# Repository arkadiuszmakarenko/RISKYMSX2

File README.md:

# RISKYMSX2

The RISKYMSX2 cartridge PROTOTYPE by Arek Makarenko is a compact MSX flash ROM cartridge based on the inexpensive CH32V467VCT6 RISC-V MCU which can be easily programmed from a MSX computer using a FAT formatted USB pen drive containing ROM files.
This chip is 200Mhz with 8MB PSRAM onboard, USB HS, and I will be figting to meet all needed MSX timings. Wish me luck!

DO NOT BUILD AT THIS STAGE unless you can create own firmware!

<<<<<<< HEAD
Piout ChatGPT
U1 CONNECTIONS
KiCad 10 schematic: RISKYMSX2.kicad_sch
Component: CH32V467VET6

Pin	MCU pin	Connection
----	-------	----------
1	PE2(FT)	WR
2	PE3(FT)	WAIT
3	PE4(FT)	~{RESET}
4	PE5(FT)	MREQ
5	PE6(FT)	M1
6	VBAT	unlabelled connection
7	PC13	NC
8	PC14	NC
9	PC15	NC
10	VSS	unlabelled connection
11	VDD	unlabelled connection
12	OSC_IN	X1 (crystal connection)
13	OSC_OUT	X1 (crystal connection)
14	~{NRST}	NRST
15	PC0	NC
16	PC1	NC
17	PC2	NC
18	PC3	NC
19	VSSA	unlabelled connection
20	VREF-	unlabelled connection
21	VREF+	unlabelled connection
22	VDDA	unlabelled connection
23	PA0	LEDFLASH
24	PA1	NC
25	PA2	NC
26	PA3	NC
27	VSS	unlabelled connection
28	VDD	unlabelled connection
29	PA4(HS)	SCC_OUT
30	PA5(HS)	NC
31	PA6(HS)	NC
32	PA7(HS)	NC
33	PC4	NC
34	PC5	NC
35	PB0	NC
36	PB1	NC
37	BOOT1(FT)	GND
38	PE8(FT)	IORQ
39	PE9(FT)	BDIR
40	VDDK	unlabelled connection
41	VSS	unlabelled connection
42	MDIRN	NC
43	MDIRP	NC
44	MDITN	NC
45	MDITP	NC
46	VDD	unlabelled connection
47	VSS	unlabelled connection
48	VDD18	unlabelled connection
49	PB10(FT)	D2
50	PB11(FT)	D3
51	PD8(FT)	A8
52	PB12(FT)	D4
53	PB13(FT)	D5
54	PB14(FT)	D6
55	PB15(FT)	D7
56	PD9(FT)	A9
57	PD10(FT)	A10
58	PD11(FT)	A11
59	PD12(FT)	A12
60	PD13(FT)	A13
61	PD14(FT)	A14
62	PD15(FT)	A15
63	PC6(FT)	CS2
64	PC7(FT)	RFSH
65	PC8(FT)	SLOTINT
66	PC9(FT)	SLOTCLK
67	PA8(FT)	NC
68	PA9(FT)	USART_TX
69	PA10(FT)	USART_RX
70	PA11	USB1_DM
71	PA12	USB1_DP
72	SWDIO(FT)	SWDIO
73	PE10(FT)	CS1
74	PE11(FT)	CS12
75	VDD	unlabelled connection
76	SWCLK(FT)	SWCLK
77	PA15(FT)	NC
78	PC10(FT)	NC
79	PC11(FT)	NC
80	PC12(FT)	NC
81	PD0(FT)	A0
82	PD1(FT)	A1
83	PD2(FT)	A2
84	PD3(FT)	A3
85	PD4(FT)	A4
86	PD5(FT)	A5
87	PD6(FT)	A6
88	PD7(FT)	A7
89	PB3(FT)	NC
90	PB4(FT)	NC
91	PB5(FT)	NC
92	PB6	NC
93	PB7	NC
94	BOOT0(FT)	BOOT0
95	PB8(FT)	D0
96	PB9(FT)	D1
97	PE0(FT)	~{EXSLTSL}
98	PE1(FT)	RD
99	VSS	unlabelled connection
100	VDD	unlabelled connection

Notes:
- NC = explicit KiCad no-connect marker.
- 'unlabelled connection' = the pin is wired, but no named net label was found on that net.
- X1 = the crystal connected to U1 pins 12 and 13.

Important: In this schematic U1 pin 34 (PC5) is NC; A0 is U1 pin 81 (PD0).
=======

>>>>>>> 920e6b2be6f260394af7e6f48916e51129308a6d

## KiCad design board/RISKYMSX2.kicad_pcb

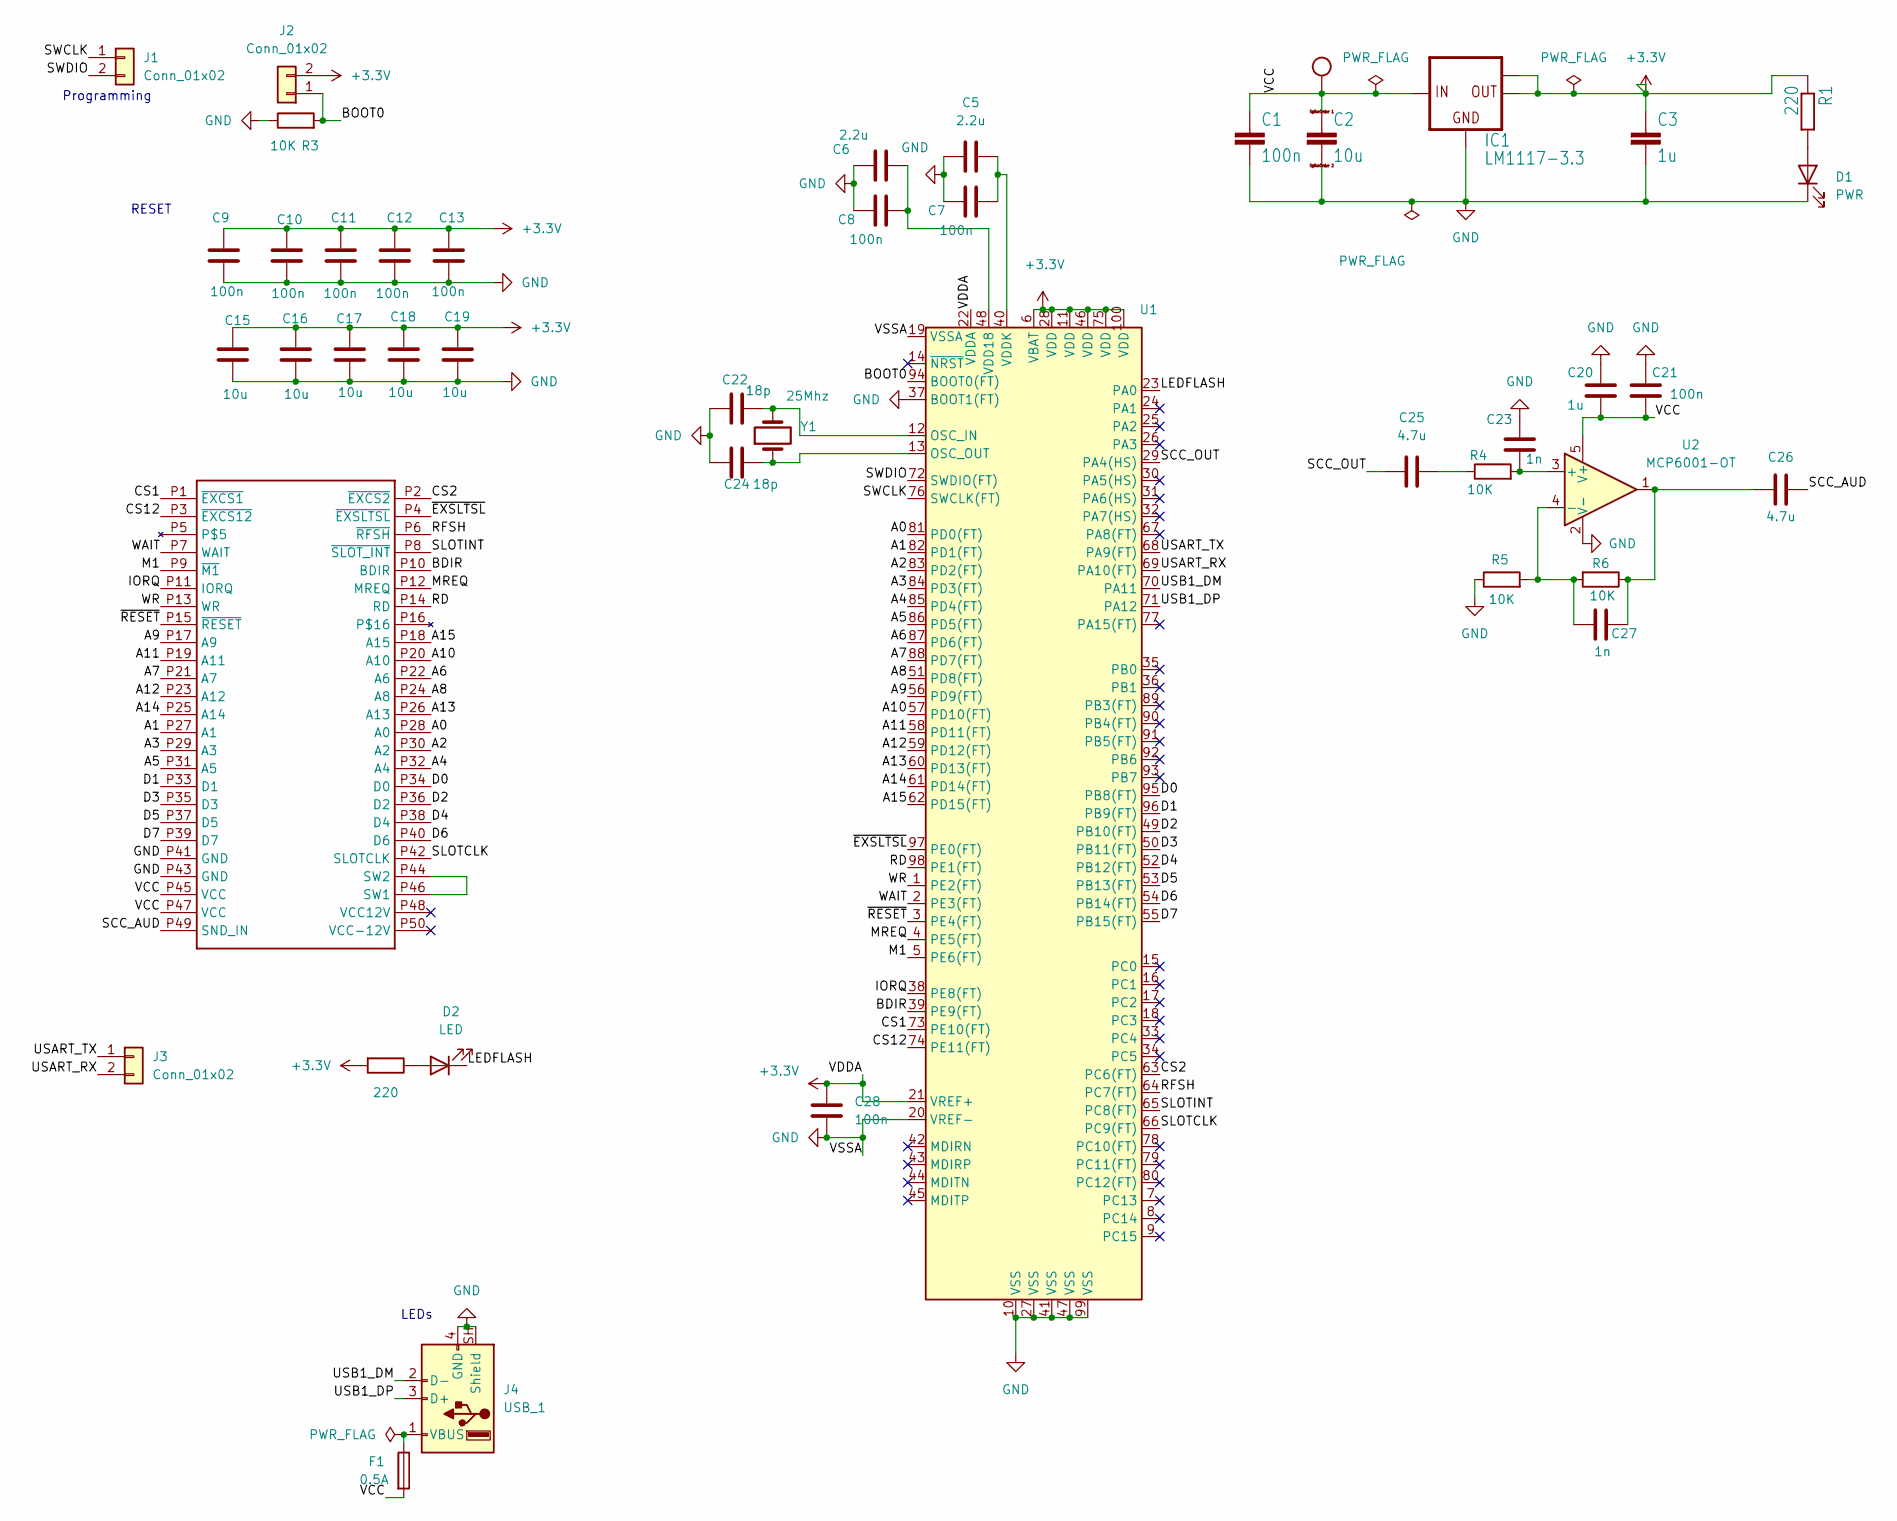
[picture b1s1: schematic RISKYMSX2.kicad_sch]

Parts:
C1: 100n; C_1206_3216Metric
C2, C15, C16, C17, C18, C19: 10u; C_0603_1608Metric_Pad1.08x0.95mm_HandSolder
C3: 1u; C_1206_3216Metric
C5, C6: 2.2u; C_0603_1608Metric_Pad1.08x0.95mm_HandSolder
C7, C8, C9, C10, C11, C12, C13, C21, C28: 100n; C_0603_1608Metric_Pad1.08x0.95mm_HandSolder
C20: 1u; C_0603_1608Metric_Pad1.08x0.95mm_HandSolder
C22, C24: 18p; C_0603_1608Metric_Pad1.08x0.95mm_HandSolder
C23, C27: 1n; C_0603_1608Metric_Pad1.08x0.95mm_HandSolder
C25, C26: 4.7u; C_0603_1608Metric_Pad1.08x0.95mm_HandSolder
CN1: MSX_CART
D1: PWR; LED_1206_3216Metric_Pad1.42x1.75mm_HandSolder
D2: LED; LED_1206_3216Metric_Pad1.42x1.75mm_HandSolder
F1: 0.5A; Fuse_1206_3216Metric_Pad1.42x1.75mm_HandSolder
IC1: LM1117-3.3; SOT223
J1, J2, J3: Conn_01x02; PinHeader_1x02_P2.54mm_Vertical
J4: USB_1; USB_A_Molex_67643_Horizontal
R1, R7: 220; R_0603_1608Metric_Pad0.98x0.95mm_HandSolder
R3, R4, R5, R6: 10K; R_0603_1608Metric_Pad0.98x0.95mm_HandSolder
U1: CH32V467VET6; LQFP-100_14x14mm_P0.5mm
U2: MCP6001-OT; SOT-23-5
Y1: 25Mhz; Crystal_HC49-4H_Vertical

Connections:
+3.3V: C3.1, C9.1, C10.1, C11.1, C12.1, C13.1, C15.1, C16.1, C17.1, C18.1, C19.1, C28.1, IC1.2 (OUT), IC1.TAB (OUT1), J2.2, R1.1, R7.2, U1.6 (VBAT), U1.11 (VDD), U1.21 (VREF+), U1.22 (VDDA), U1.28 (VDD), U1.46 (VDD), U1.75 (VDD), U1.100 (VDD)
/A0: CN1.P28 (A0), U1.81 (PD0(FT))
/A1: CN1.P27 (A1), U1.82 (PD1(FT))
/A2: CN1.P30 (A2), U1.83 (PD2(FT))
/A3: CN1.P29 (A3), U1.84 (PD3(FT))
/A4: CN1.P32 (A4), U1.85 (PD4(FT))
/A5: CN1.P31 (A5), U1.86 (PD5(FT))
/A6: CN1.P22 (A6), U1.87 (PD6(FT))
/A7: CN1.P21 (A7), U1.88 (PD7(FT))
/A8: CN1.P24 (A8), U1.51 (PD8(FT))
/A9: CN1.P17 (A9), U1.56 (PD9(FT))
/A10: CN1.P20 (A10), U1.57 (PD10(FT))
/A11: CN1.P19 (A11), U1.58 (PD11(FT))
/A12: CN1.P23 (A12), U1.59 (PD12(FT))
/A13: CN1.P26 (A13), U1.60 (PD13(FT))
/A14: CN1.P25 (A14), U1.61 (PD14(FT))
/A15: CN1.P18 (A15), U1.62 (PD15(FT))
/BDIR: CN1.P10 (BDIR), U1.39 (PE9(FT))
/BOOT0: J2.1, R3.2, U1.94 (BOOT0(FT))
/CS1: CN1.P1 (~EXCS1), U1.73 (PE10(FT))
/CS2: CN1.P2 (~EXCS2), U1.63 (PC6(FT))
/CS12: CN1.P3 (~EXCS12), U1.74 (PE11(FT))
/D0: CN1.P34 (D0), U1.95 (PB8(FT))
/D1: CN1.P33 (D1), U1.96 (PB9(FT))
/D2: CN1.P36 (D2), U1.49 (PB10(FT))
/D3: CN1.P35 (D3), U1.50 (PB11(FT))
/D4: CN1.P38 (D4), U1.52 (PB12(FT))
/D5: CN1.P37 (D5), U1.53 (PB13(FT))
/D6: CN1.P40 (D6), U1.54 (PB14(FT))
/D7: CN1.P39 (D7), U1.55 (PB15(FT))
/IORQ: CN1.P11 (IORQ), U1.38 (PE8(FT))
/LEDFLASH: D2.1 (K), U1.23 (PA0)
/M1: CN1.P9 (~M1), U1.5 (PE6(FT))
/MREQ: CN1.P12 (MREQ), U1.4 (PE5(FT))
/RD: CN1.P14 (RD), U1.98 (PE1(FT))
/RFSH: CN1.P6 (~RFSH), U1.64 (PC7(FT))
/SCC_AUD: C26.2, CN1.P49 (SND_IN)
/SCC_OUT: C25.1, U1.29 (PA4(HS))
/SLOTCLK: CN1.P42 (SLOTCLK), U1.66 (PC9(FT))
/SLOTINT: CN1.P8 (~SLOT_INT), U1.65 (PC8(FT))
/SWCLK: J1.1, U1.76 (SWCLK(FT))
/SWDIO: J1.2, U1.72 (SWDIO(FT))
/USART_RX: J3.2, U1.69 (PA10(FT))
/USART_TX: J3.1, U1.68 (PA9(FT))
/USB1_DM: J4.2 (D-), U1.70 (PA11)
/USB1_DP: J4.3 (D+), U1.71 (PA12)
/WAIT: CN1.P7 (WAIT), U1.2 (PE3(FT))
/WR: CN1.P13 (WR), U1.1 (PE2(FT))
/~EXSLTSL: CN1.P4 (~EXSLTSL), U1.97 (PE0(FT))
/~RESET: CN1.P15 (~RESET), U1.3 (PE4(FT))
GND: C1.2, C2.2, C3.2, C5.1, C6.1, C7.1, C8.1, C9.2, C10.2, C11.2, C12.2, C13.2, C15.2, C16.2, C17.2, C18.2, C19.2, C20.1, C21.1, C22.1, C23.2, C24.1, C28.2, CN1.P41 (GND), CN1.P43 (GND), D1.1 (K), IC1.1 (GND), J4.4 (GND), J4.SH (Shield), R3.1, R5.1, U1.10 (VSS), U1.19 (VSSA), U1.20 (VREF-), U1.27 (VSS), U1.37 (BOOT1(FT)), U1.41 (VSS), U1.47 (VSS), U1.99 (VSS), U2.2 (V-)
unnamed: C25.2, R4.1
unnamed: C26.1, C27.2, R6.1, U2.1
unnamed: CN1.P44 (SW2), CN1.P46 (SW1)
unnamed: D1.2 (A), R1.2
unnamed: D2.2 (A), R7.1
unnamed: F1.1, J4.1 (VBUS)
unnamed: C22.2, U1.12 (OSC_IN), Y1.2
unnamed: C24.2, U1.13 (OSC_OUT), Y1.1
unnamed: C6.2, C8.2, U1.48 (VDD18)
unnamed: C5.2, C7.2, U1.40 (VDDK)
unnamed: C23.1, R4.2, U2.3 (+)
unnamed: C27.1, R5.2, R6.2, U2.4 (-)
VCC: C1.1, C2.1, C20.2, C21.2, CN1.P45 (VCC), CN1.P47 (VCC), F1.2, IC1.3 (IN), U2.5 (V+)

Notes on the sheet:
RESET
Programming
LEDs

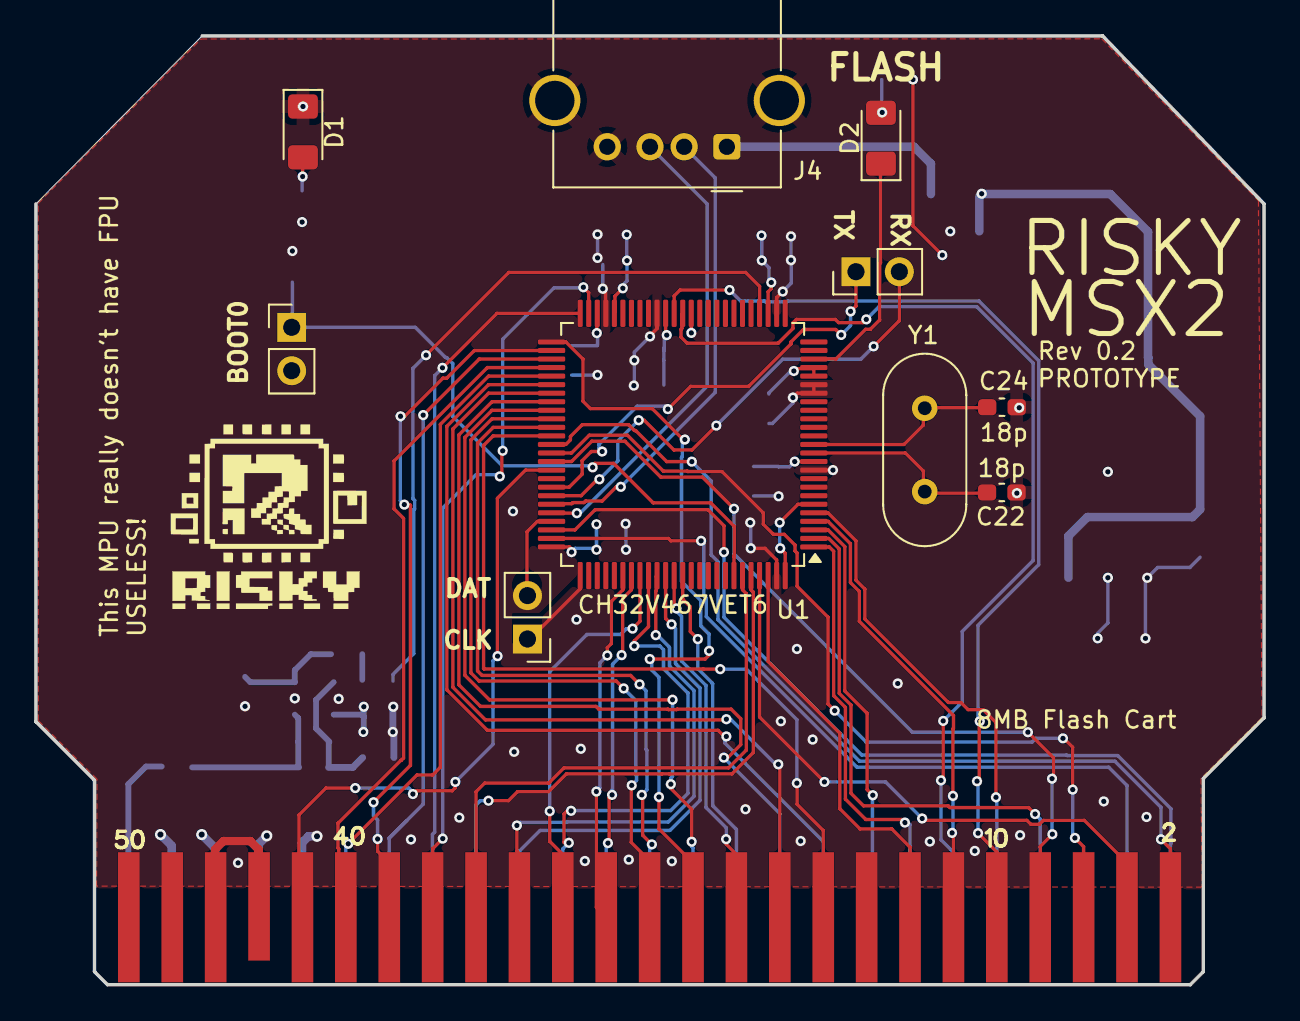
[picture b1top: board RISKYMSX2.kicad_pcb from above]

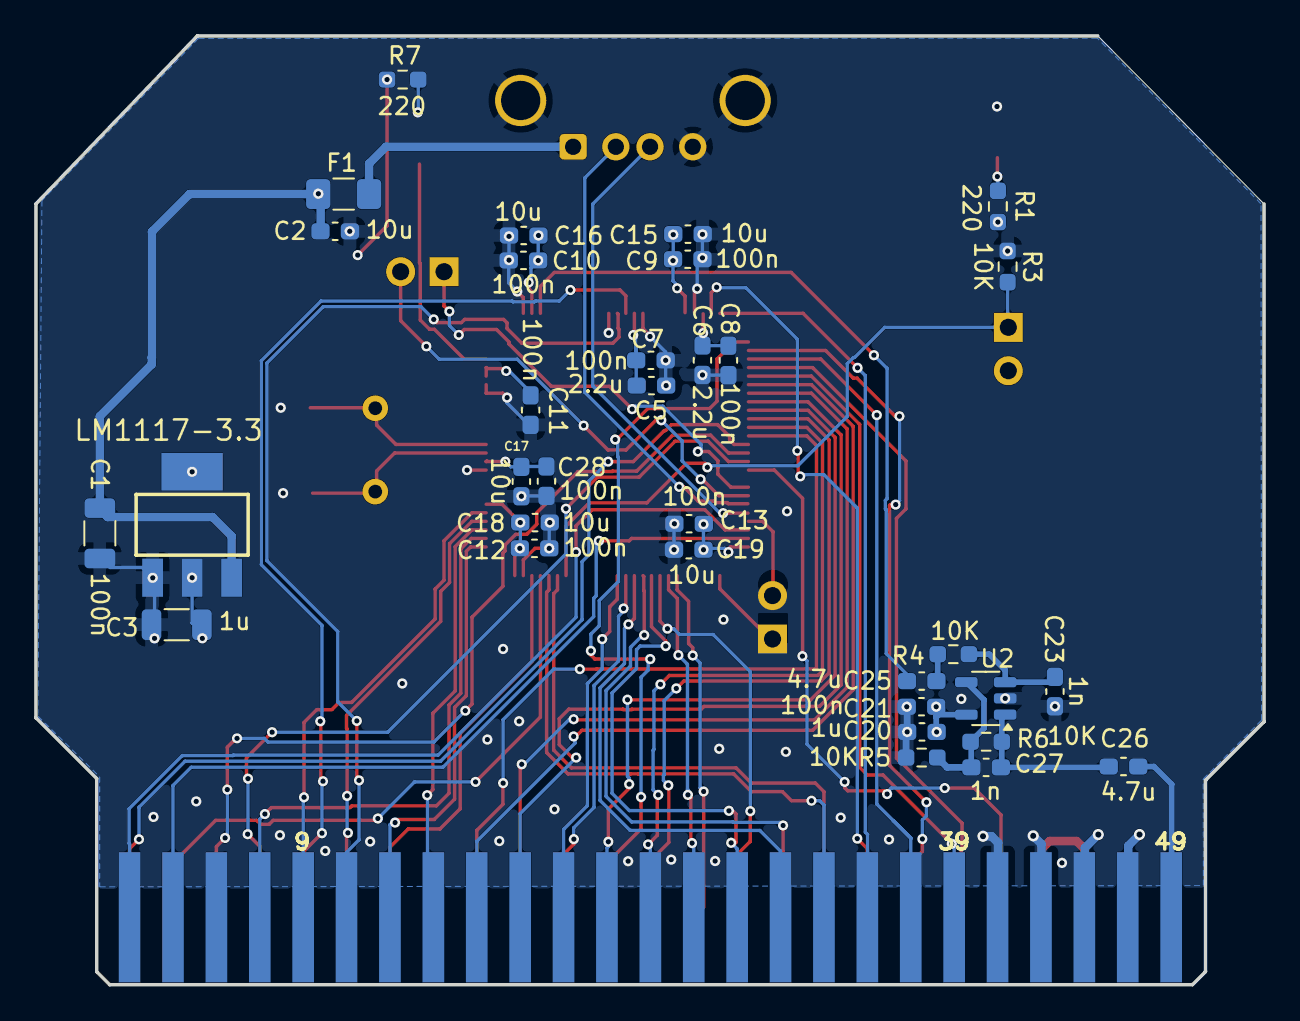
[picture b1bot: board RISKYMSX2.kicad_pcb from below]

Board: 4 copper layers, 71.9 x 55.5 mm, 44 parts (33 on the bottom side), 64 nets.

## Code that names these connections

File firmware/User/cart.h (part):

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/*
 * CH32V407VET6 (RISKYMSX2) MSX cartridge bus pinout.
 *
 *   PD0..PD15   A0..A15   (16-bit address bus)  -> GPIOD->INDR
 *   PB8..PB15   D0..D7    (8-bit data bus)      -> GPIOB OUTDR[15:8]
 *
 *   PE0  (pin 97)  ~SLTSL   slot select          -> EXTI0 trigger
 *   PE1  (pin 98)  RD
 *   PE2  (pin  1)  WR
 *   PE3  (pin  2)  ~WAIT     bus-cycle stretch   -> GPIO (low output/input)
 *   PE5  (pin  4)  MREQ
 *   PE6  (pin  3)  M1        (low during opcode fetch)
 *
 *   PA0  (pin 23)  LEDFLASH (status LED)
 */

/* Control-bus bit masks within GPIOE->INDR */
#define CART_SLTSL_MASK   0x0001U  /* PE0  ~SLTSL  (slot select, EXTIO trigger) */
#define CART_RD_MASK      0x0002U  /* PE1  ~RD */
#define CART_WR_MASK      0x0004U  /* PE2  ~WR */
#define CART_WAIT_MASK    0x0008U  /* PE3  ~WAIT (active-low cart output) */
#define CART_RESET_MASK   0x0010U  /* PE4  ~RESET (TFMSX dev hardware only) */
#define CART_MREQ_MASK    0x0020U  /* PE5  ~MREQ  (memory-cycle qualifier)  */
#define CART_M1_MASK      0x0040U  /* PE6  M1 (low during opcode fetch) */
#define CART_IORQ_MASK    0x0100U  /* PE8  ~IORQ  (I/O-cycle qualifier)
                                    * currently unused: the Sunrise IDE
                                    * mapper decodes the IDE register /
                                    * data window purely by address, not
                                    * by qualifying ~IORQ. The bit is
                                    * still wired on the cart edge (PE8)
                                    * but the EXTI8 IORQ decoder was
                                    * removed together with the legacy
                                    * ASCII16 memory-mapper protocol
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 * capture start from the first Z80 cycle instead of being armed against a
 * hand-pressed reset button.
 *
 * PE4 is ALWAYS driven open-drain: the pin can only pull the line low and
 * never drives it high, so it cannot fight the mainboard's own reset
 * driver. Even so, this is only safe on boards that actually wire ~RESET
 * as drivable (TFMSX-style development hardware). On a production
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#define CART_MSX_RESET_ARM_DELAY_MS 20000U
#endif

/* Drive MSX ~RESET (PE4) low / release it. Release returns the pin to a
 * floating input, never a driven high level. */
void Cart_MSXReset_Assert (void);
void Cart_MSXReset_Release (void);
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 *       which the real hardware decodes as the sound chip). Every
 *       cartridge write is queued for the SCC emulator core (emu2212,
 *       ported verbatim from v303Firmware), which renders samples to
 *       DAC1/PA4 (SCC_OUT) at a timer-derived ~44.1 kHz rate - see
 *       scc.c/scc.h.
 *
 * Note: ROM16k maps a 16 KiB image at 0x4000..0x7FFF (page 1) and the
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 * of the swap. That path is REMOVED: most MSX2+ machines expose the
 * cart-edge ~RESET as read-only and driving it externally can
 * damage the mainboard. The CMD_SOFTRESET slingshot (running from
 * MSX RAM) provides the equivalent atomicity without touching PE4.
 *
 * Returns the same value as Cart_SetMapper(). */
int  Cart_SetMapper_Safe (Cart_Mapper m);
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 * handler. The caller then installs Nextor; its kernel ROM is flash-served,
 * while the mapper-RAM sub-slot is enabled after PSRAM initialization.
 *
 * NOTE: PE4 (MSX ~RESET) is configured here as a floating input only.
 * The firmware never drives it (read-only on most MSX2+ machines;
 * driving it externally can damage the mainboard). See
 * Cart_SetMapper_Safe for the cart-swap primitive that closes the
 * race window without touching PE4, and loader.c::cmd_softreset for
 * the CMD_SOFTRESET reboot path.
 *
 * PE3 (~WAIT) is configured as a floating input during normal startup; this
 * firmware does not hold the MSX while peripherals initialize. */
void Init_Cart (void);

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void CartServiceLoop(void) __attribute__((section(".ramfunc"), noinline));

/* NOTE: there is intentionally no Cart_AssertMSXReset* API in this
 * header. The firmware never drives MSX ~RESET (PE4 is read-only on
 * most MSX2+ machines; driving it externally can damage the
 * mainboard). Reboot is via the MSX-side loader's CMD_SOFTRESET
 * slingshot (loader.c). */
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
